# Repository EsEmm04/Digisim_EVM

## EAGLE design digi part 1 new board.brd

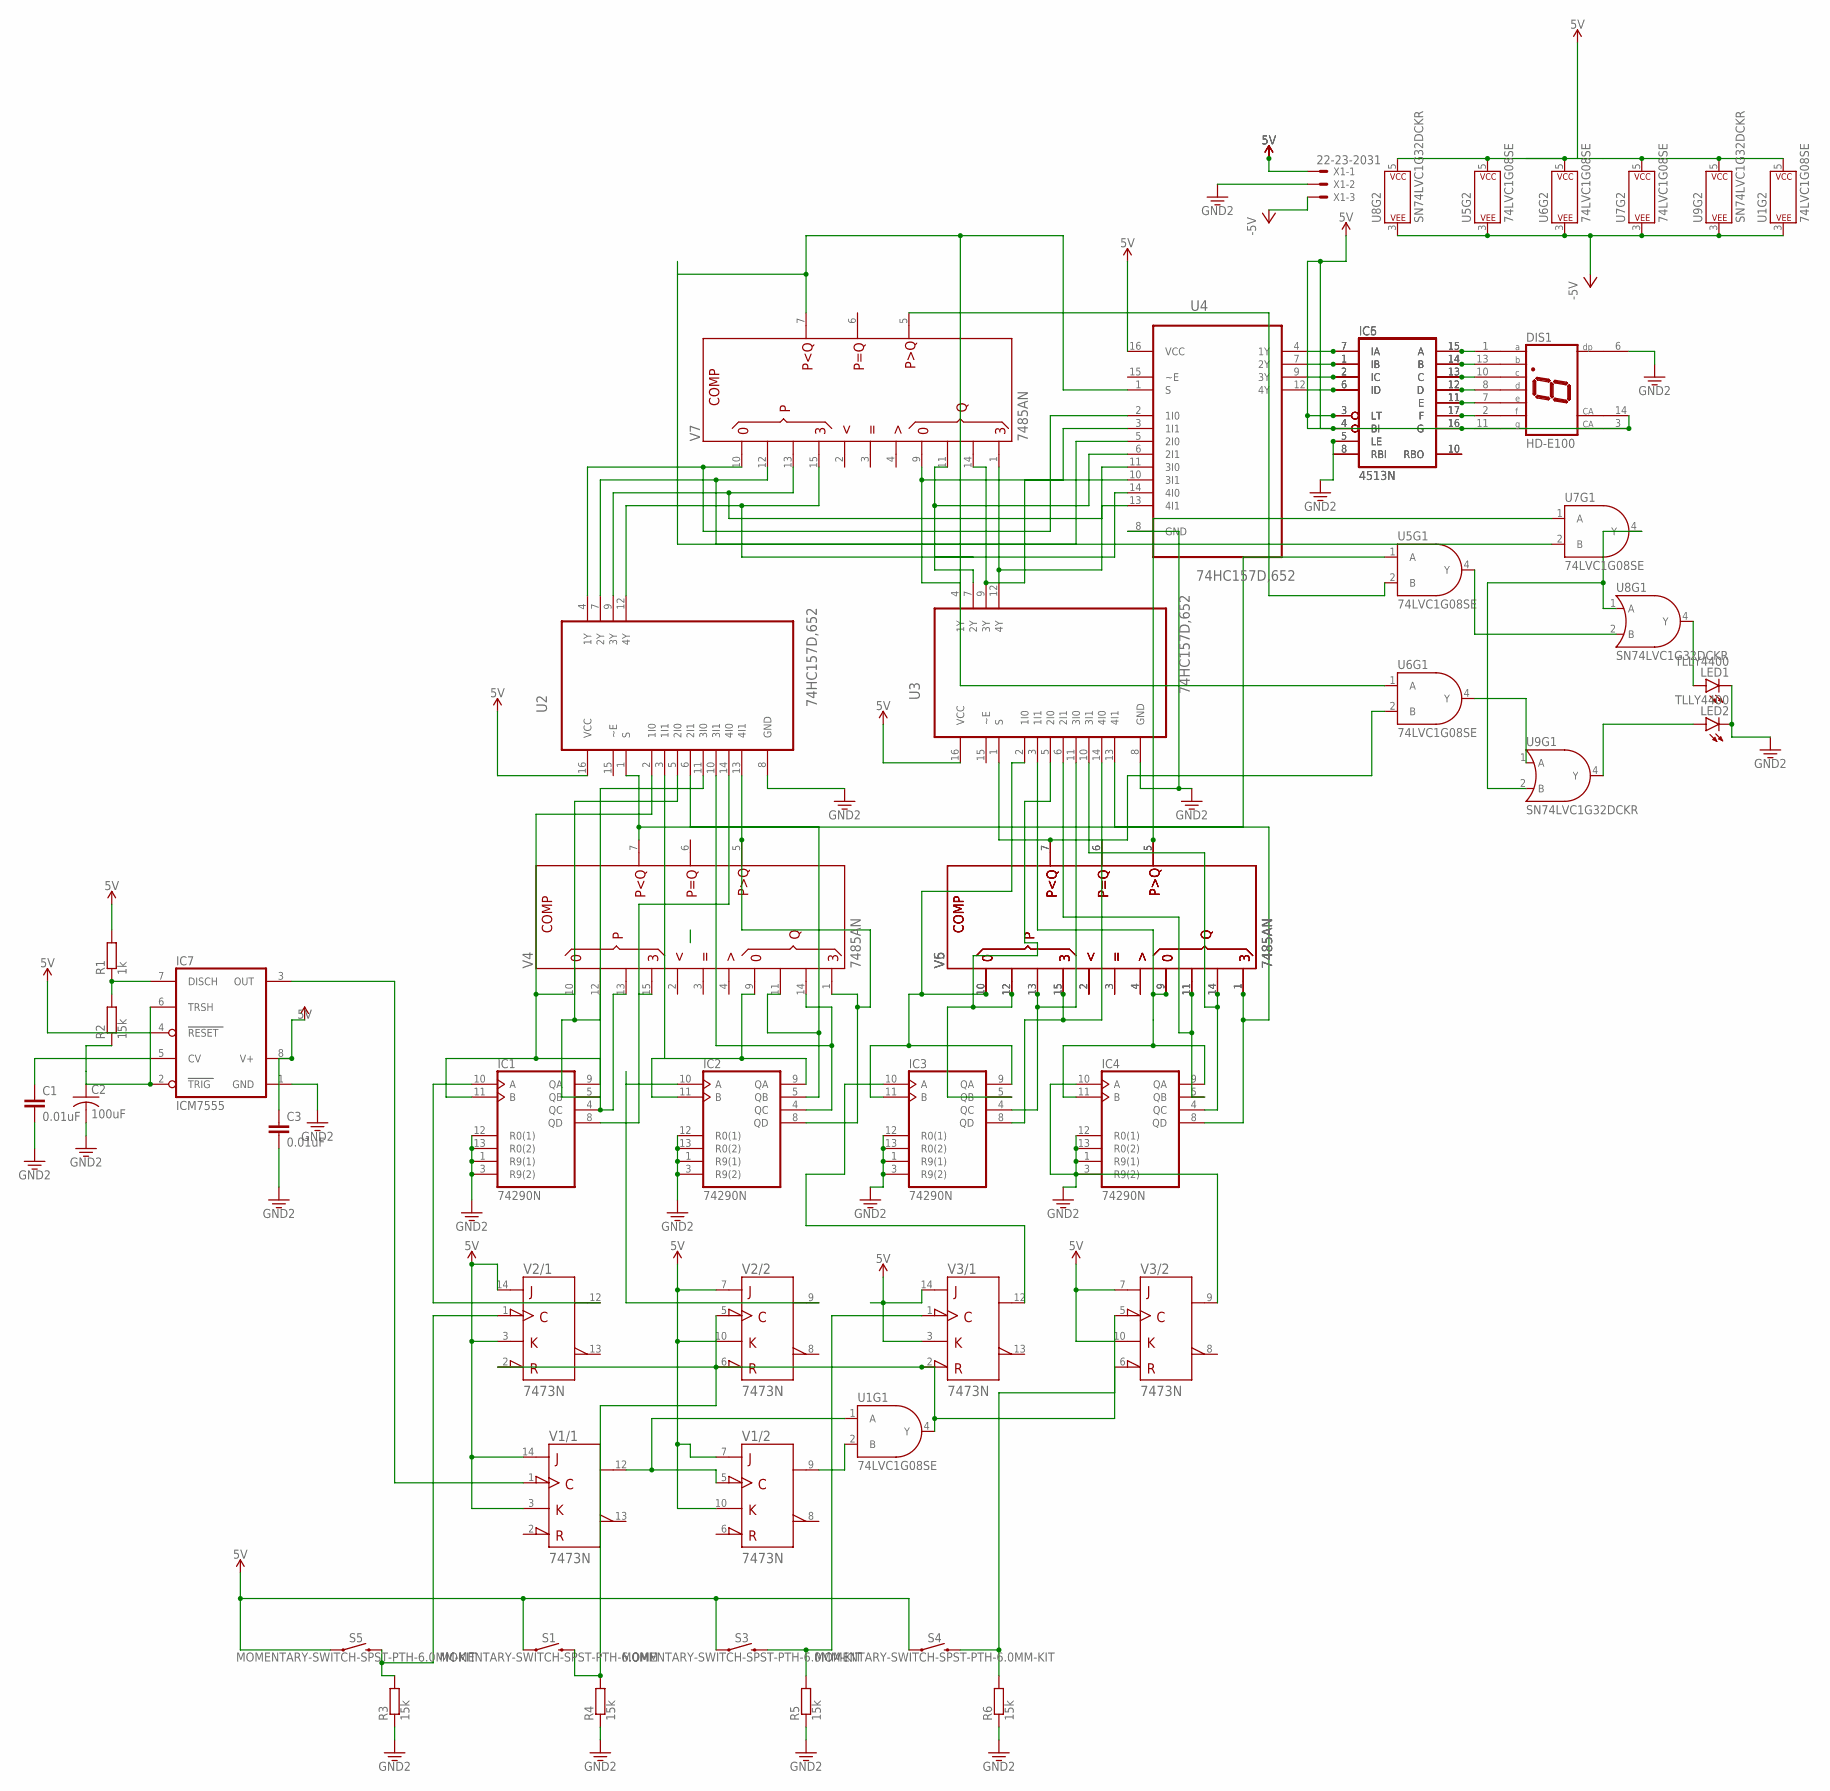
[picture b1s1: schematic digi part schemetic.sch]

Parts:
C1, C3: 0.01uF; 0805
C2: 100uF; C075-032X103
DIS1: HD-E100; HDSP-I
IC1, IC2, IC3, IC4: 74290N; DIL14
IC5, IC6: 4513N; DIL18
IC7: ICM7555; DIL08
LED1, LED2: TLLY4400; LED3MM
R1: 1k; SMK
R2, R3, R4, R5, R6: 15k; SMK
S1: MOMENTARY-SWITCH-SPST-PTH-6.0MM; TACTILE_SWITCH_PTH_6.0MM
S3, S4, S5: MOMENTARY-SWITCH-SPST-PTH-6.0MM-KIT; TACTILE_SWITCH_PTH_6.0MM_KIT
U1, U5, U6, U7: 74LVC1G08SE; SOT23-5
U2, U3, U4: 74HC157D,652; SOIC127P600X175-16N
U8, U9: SN74LVC1G32DCKR; SOT23-5
V1, V2, V3: 7473N; DIL14
V4, V5, V6, V7: 7485AN; DIL16
X1: 22-23-2031

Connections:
3.3V: C1.2, C2.2, C3.2, DIS1.6 (DP), IC1.1 (R9(1)), IC1.3 (R9(2)), IC1.12 (R0(1)), IC1.13 (R0(2)), IC2.1 (R9(1)), IC2.3 (R9(2)), IC2.12 (R0(1)), IC2.13 (R0(2)), IC3.1 (R9(1)), IC3.3 (R9(2)), IC3.12 (R0(1)), IC3.13 (R0(2)), IC4.1 (R9(1)), IC4.3 (R9(2)), IC4.12 (R0(1)), IC4.13 (R0(2)), IC5.5 (LE), IC6.5 (LE), IC7.1 (GND), LED1.K (C), LED2.K (C), R3.2, R4.2, R5.2, R6.2, U2.8 (GND), U3.8 (GND), U4.8 (GND), X1.2
5V: C3.1, DIS1.3 (CA), DIS1.14 (CA), IC5.3 (LT), IC5.4 (BI), IC6.3 (LT), IC6.4 (BI), IC7.4 (RESET), IC7.8 (V+), R1.1, S1.1, S3.1, S4.1, S5.1, U1.5 (P$V+), U2.16 (VCC), U3.16 (VCC), U4.16 (VCC), U5.5 (P$V+), U6.5 (P$V+), U7.5 (P$V+), U8.5 (P$V+), U9.5 (P$V+), V1.3 (K), V1.7 (J), V1.10 (K), V1.14 (J), V2.3 (K), V2.7 (J), V2.10 (K), V2.14 (J), V3.3 (K), V3.7 (J), V3.10 (K), V3.14 (J), X1.1
+UB: V1.4 (+UB), V2.4 (+UB), V3.4 (+UB), V4.16 (+UB), V5.16 (+UB), V6.16 (+UB), V7.16 (+UB)
-5V: U1.3 (P$V-), U5.3 (P$V-), U6.3 (P$V-), U7.3 (P$V-), U8.3 (P$V-), U9.3 (P$V-), X1.3
-UB: V1.11 (-UB), V2.11 (-UB), V3.11 (-UB), V4.8 (-UB), V5.8 (-UB), V6.8 (-UB), V7.8 (-UB)
GND: IC1.7 (GND), IC2.7 (GND), IC3.7 (GND), IC4.7 (GND)
unnamed: U1.1 (A), V1.5 (CLK), V1.12 (Q)
unnamed: U1.2 (B), V1.9 (Q)
unnamed: U1.4 (Y), V2.2 (!CLR), V2.6 (!CLR), V3.2 (!CLR), V3.6 (!CLR)
unnamed: IC1.10 (A), V2.12 (Q)
unnamed: IC1.9 (QA), IC1.11 (B), U2.2 (1I0), V4.10 (P0)
unnamed: IC2.9 (QA), IC2.11 (B), U2.3 (1I1), V4.9 (Q0)
unnamed: U4.1 (S), U6.1 (A), U7.2 (B), V7.7 (PLTQ)
unnamed: IC4.9 (QA), IC4.11 (B), U3.3 (1I1), V5.9 (Q0), V6.9 (Q0)
unnamed: IC2.10 (A), V2.9 (Q)
unnamed: IC3.10 (A), V3.12 (Q)
unnamed: IC4.10 (A), V3.9 (Q)
unnamed: IC4.8 (QD), U3.13 (4I1), V5.1 (Q3), V6.1 (Q3)
unnamed: IC1.4 (QC), U2.11 (3I0), V4.13 (P2)
unnamed: IC4.4 (QC), U3.10 (3I1), V5.14 (Q2), V6.14 (Q2)
unnamed: IC4.5 (QB), U3.6 (2I1), V5.11 (Q1), V6.11 (Q1)
unnamed: U2.1 (S), U5.1 (A), V4.7 (PLTQ)
unnamed: V5.4 (PGTQ_), V6.4 (PGTQ_)
unnamed: V5.3 (PEQQ_), V6.3 (PEQQ_)
unnamed: V5.2 (PLTQ_), V6.2 (PLTQ_)
unnamed: IC3.8 (QD), U3.14 (4I0), V5.15 (P3), V6.15 (P3)
unnamed: IC3.4 (QC), U3.11 (3I0), V5.13 (P2), V6.13 (P2)
unnamed: IC3.5 (QB), U3.5 (2I0), V5.12 (P1), V6.12 (P1)
unnamed: IC3.9 (QA), IC3.11 (B), U3.2 (1I0), V5.10 (P0), V6.10 (P0)
unnamed: U3.1 (S), U6.2 (B), V5.7 (PLTQ), V6.7 (PLTQ)
unnamed: V5.6 (PEQQ), V6.6 (PEQQ)
unnamed: U7.1 (A), V5.5 (PGTQ), V6.5 (PGTQ)
unnamed: IC1.5 (QB), U2.5 (2I0), V4.12 (P1)
unnamed: IC2.8 (QD), U2.13 (4I1), V4.1 (Q3), V4.5 (PGTQ)
unnamed: IC2.4 (QC), U2.10 (3I1), V4.14 (Q2)
unnamed: IC1.8 (QD), U2.14 (4I0), V4.15 (P3)
unnamed: IC2.5 (QB), U2.6 (2I1), V4.11 (Q1)
unnamed: IC5.1 (IB), IC6.1 (IB), U4.7 (2Y)
unnamed: U3.7 (2Y), U4.6 (2I1), V7.11 (Q1)
unnamed: IC5.2 (IC), IC6.2 (IC), U4.9 (3Y)
unnamed: U5.2 (B), V7.5 (PGTQ)
unnamed: U2.4 (1Y), U4.2 (1I0), V7.10 (P0)
unnamed: U2.7 (2Y), U4.5 (2I0), V7.12 (P1)
unnamed: U2.9 (3Y), U4.11 (3I0), V7.13 (P2)
unnamed: U2.12 (4Y), U4.14 (4I0), V7.15 (P3)
unnamed: U3.4 (1Y), U4.3 (1I1), V7.9 (Q0)
unnamed: U3.9 (3Y), U4.10 (3I1), V7.14 (Q2)
unnamed: U3.12 (4Y), U4.13 (4I1), V7.1 (Q3)
unnamed: LED2.A, U9.4 (Y)
unnamed: IC5.6 (ID), IC6.6 (ID), U4.12 (4Y)
unnamed: IC5.7 (IA), IC6.7 (IA), U4.4 (1Y)
unnamed: IC5.8 (RBI), IC6.8 (RBI)
unnamed: IC5.10 (RBO), IC6.10 (RBO)
unnamed: DIS1.7 (E), IC5.11 (E), IC6.11 (E)
unnamed: DIS1.8 (D), IC5.12 (D), IC6.12 (D)
unnamed: DIS1.10 (C), IC5.13 (C), IC6.13 (C)
unnamed: DIS1.13 (B), IC5.14 (B), IC6.14 (B)
unnamed: DIS1.1 (A), IC5.15 (A), IC6.15 (A)
unnamed: DIS1.11 (G), IC5.16 (G), IC6.16 (G)
unnamed: DIS1.2 (F), IC5.17 (F), IC6.17 (F)
unnamed: U5.4 (Y), U8.2 (B)
unnamed: U7.4 (Y), U8.1 (A), U9.2 (B)
unnamed: U6.4 (Y), U9.1 (A)
unnamed: LED1.A, U8.4 (Y)
unnamed: IC7.3 (OUT), V1.1 (CLK)
unnamed: C1.1, IC7.5 (CV)
unnamed: R3.1, S5.3 (2), V2.1 (CLK)
unnamed: IC7.7 (DISCH), R1.2, R2.1
unnamed: C2.1, IC7.2 (TRIG), IC7.6 (TRSH), R2.2
unnamed: R5.1, S3.3 (2), V3.1 (CLK)
unnamed: R6.1, S4.3 (2), V3.5 (CLK)
unnamed: R4.1, S1.3 (2), V2.5 (CLK)
VCC: IC1.14 (VCC), IC2.14 (VCC), IC3.14 (VCC), IC4.14 (VCC)
VDD: IC5.18 (VDD), IC6.18 (VDD)
VSS: IC5.9 (VSS), IC6.9 (VSS)

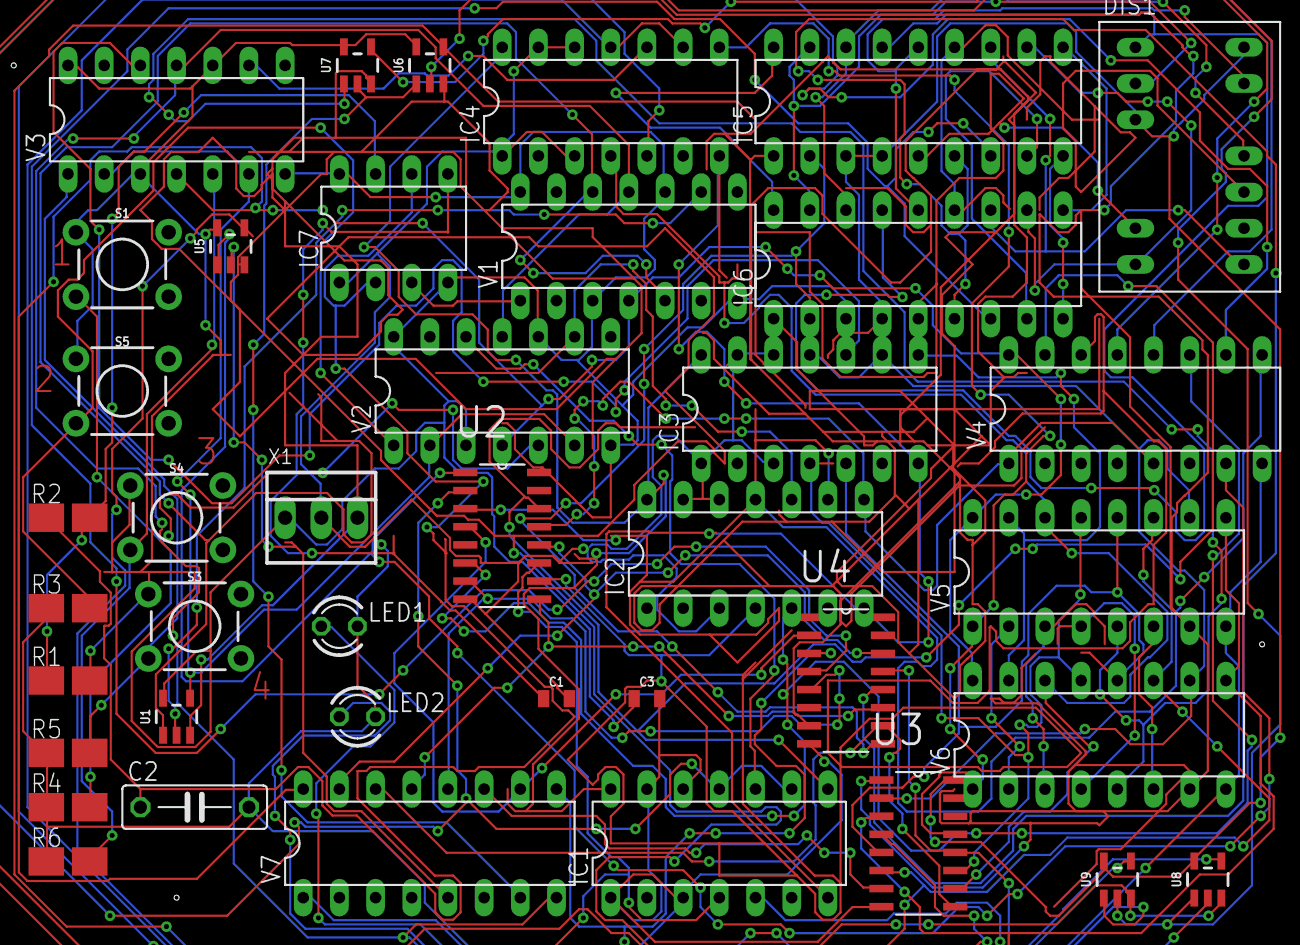
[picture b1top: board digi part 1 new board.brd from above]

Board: 2 copper layers, 40 parts (0 on the bottom side), 75 nets.

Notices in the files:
parts and their libraries:
SparkFun-Capacitors: Licensing: Creative Commons ShareAlike 4.0 International - https://creativecommons.org/licenses/by-sa/4.0
